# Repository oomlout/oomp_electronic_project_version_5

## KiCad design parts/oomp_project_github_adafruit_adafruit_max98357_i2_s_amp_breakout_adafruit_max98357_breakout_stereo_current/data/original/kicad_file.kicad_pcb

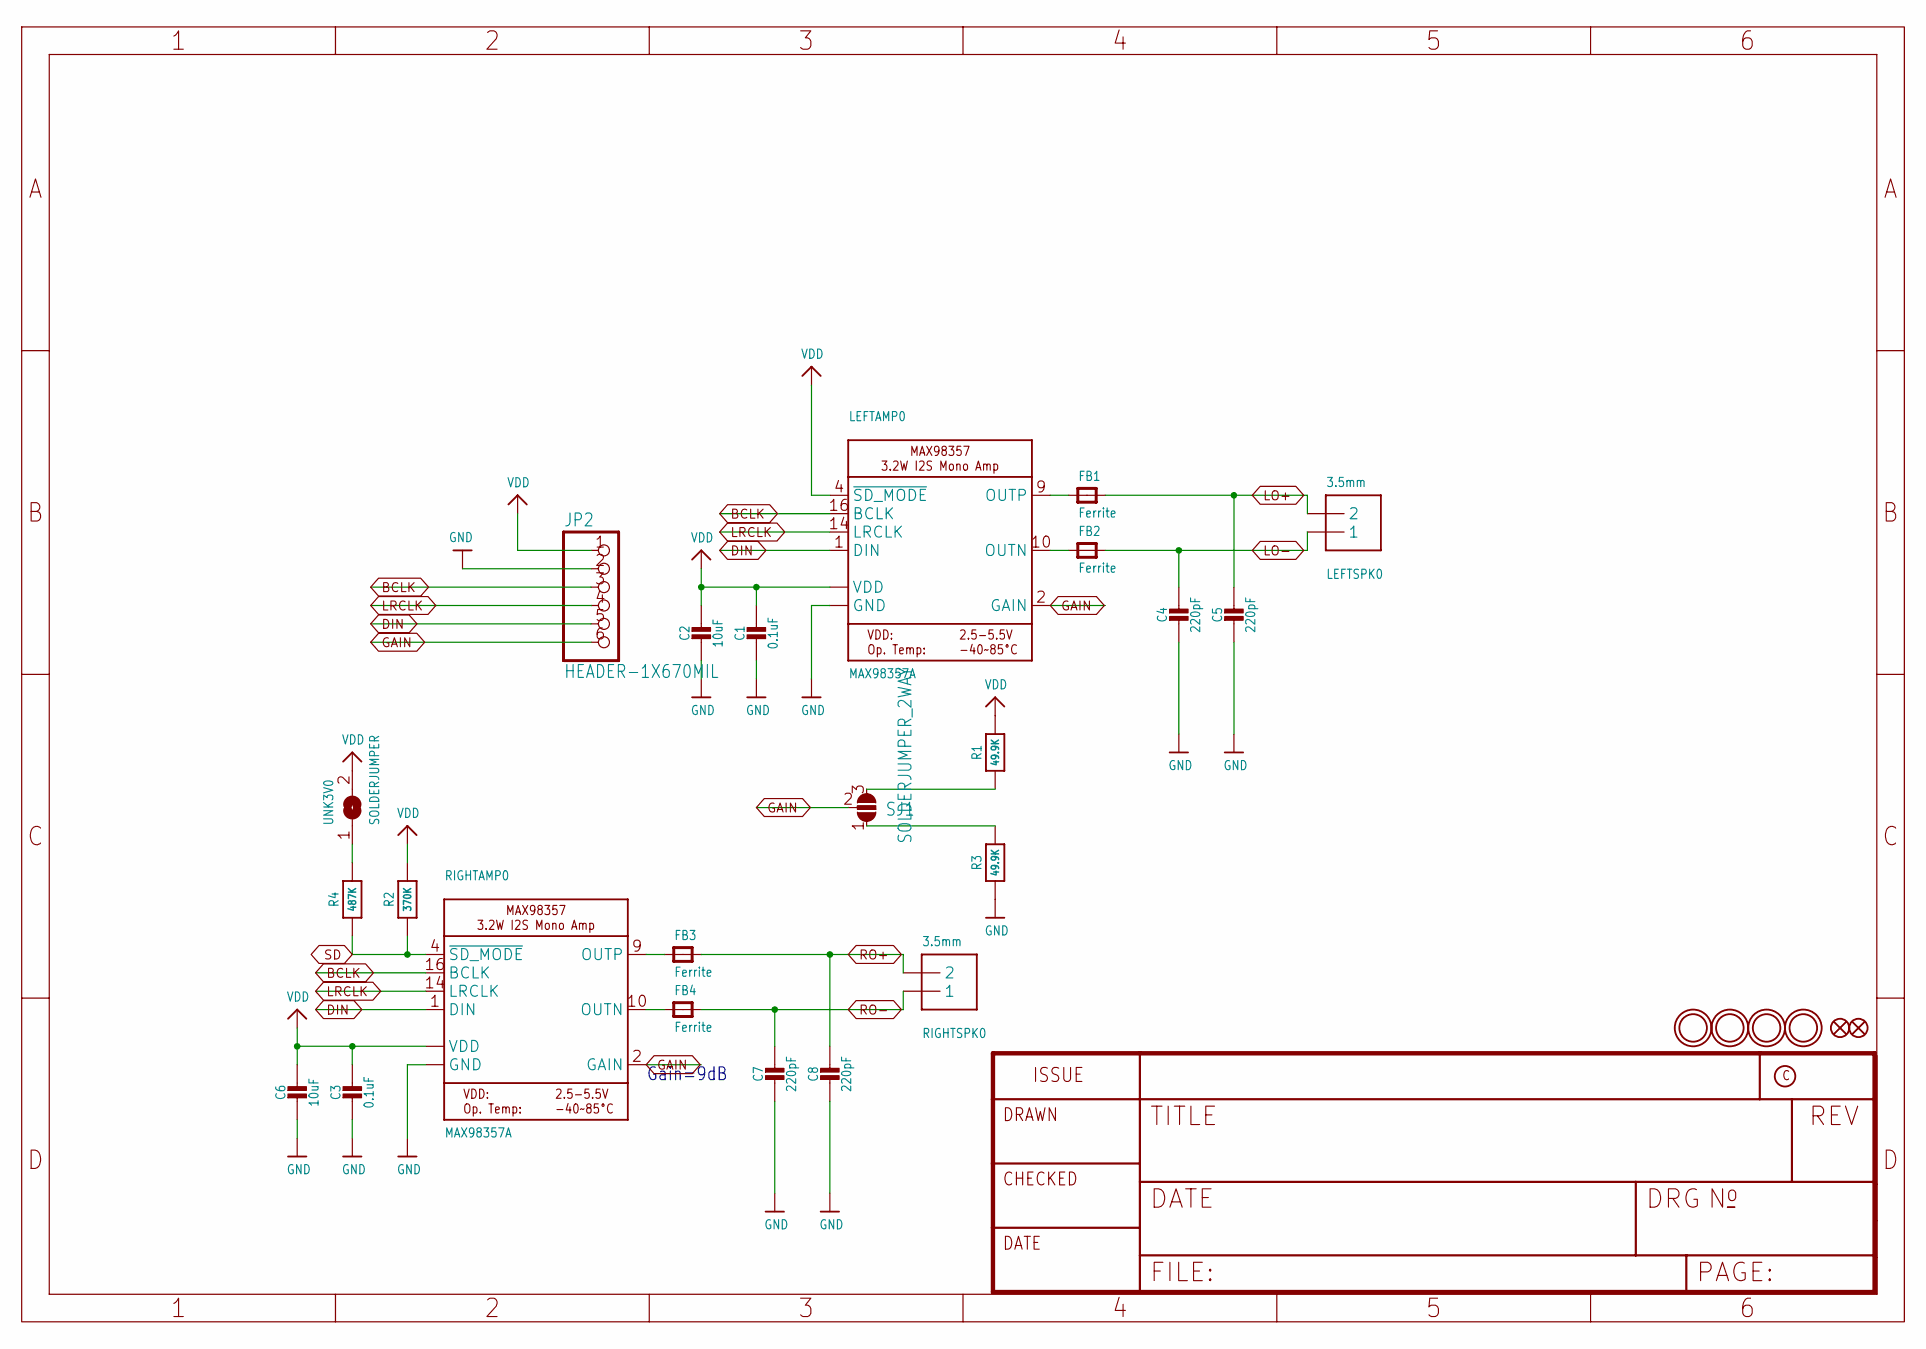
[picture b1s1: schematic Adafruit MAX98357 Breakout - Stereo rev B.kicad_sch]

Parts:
C1, C3: 0.1uF; 0603-NO
C2, C6: 10uF; 0805-NO
C4, C5, C7, C8: 220pF; 0603-NO
FB1, FB2, FB3, FB4: Ferrite; 0603-NO
FID1, FID2: FIDUCIAL_0.5MM
JP2: HEADER-1X670MIL; 1X06_ROUND_70
LEFTAMP0: MAX98357A; QFN16_3MM
LEFTSPK0: 3.5mm; TERMBLOCK_1X2-3.5MM
R1, R3: 49.9K; 0603-NO
R2: 370K; 0603-NO
R4: 487K; 0603-NO
RIGHTAMP0: MAX98357A; QFN16_3MM
RIGHTSPK0: 3.5mm; TERMBLOCK_1X2-3.5MM
SJ1: SOLDERJUMPER_2WAY; SOLDERJUMPER_2WAY_OPEN_NOPASTE
U$9, U$10, U$23, U$24: MOUNTINGHOLE2.5; MOUNTINGHOLE_2.5_PLATED
UNK3V0: SOLDERJUMPER; SOLDERJUMPER_ARROW_NOPASTE

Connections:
BCLK: JP2.3, LEFTAMP0.16 (BCLK), RIGHTAMP0.16 (BCLK)
DIN: JP2.5, LEFTAMP0.1 (DIN), RIGHTAMP0.1 (DIN)
GAIN: JP2.6, LEFTAMP0.2 (GAIN), RIGHTAMP0.2 (GAIN), SJ1.2
GND: C1.2, C2.2, C3.2, C4.2, C5.2, C6.2, C7.2, C8.2, JP2.2, LEFTAMP0.3 (GND), LEFTAMP0.11 (GND), LEFTAMP0.15 (GND), LEFTAMP0.THERMAL (GND), R3.1, RIGHTAMP0.3 (GND), RIGHTAMP0.11 (GND), RIGHTAMP0.15 (GND), RIGHTAMP0.THERMAL (GND)
LO+: C5.1, FB1.2, LEFTSPK0.2
LO-: C4.1, FB2.2, LEFTSPK0.1
LRCLK: JP2.4, LEFTAMP0.14 (LRCLK), RIGHTAMP0.14 (LRCLK)
unnamed: FB4.1, RIGHTAMP0.10 (OUTN)
unnamed: FB3.1, RIGHTAMP0.9 (OUTP)
unnamed: R3.2, SJ1.1
unnamed: R4.2, UNK3V0.1
unnamed: FB2.1, LEFTAMP0.10 (OUTN)
unnamed: FB1.1, LEFTAMP0.9 (OUTP)
unnamed: R1.1, SJ1.3
RO+: C8.1, FB3.2, RIGHTSPK0.2
RO-: C7.1, FB4.2, RIGHTSPK0.1
SD: R2.1, R4.1, RIGHTAMP0.4 (~SD_MODE)
VDD: C1.1, C2.1, C3.1, C6.1, JP2.1, LEFTAMP0.4 (~SD_MODE), LEFTAMP0.7 (VDD), LEFTAMP0.8 (VDD), R1.2, R2.2, RIGHTAMP0.7 (VDD), RIGHTAMP0.8 (VDD), UNK3V0.2

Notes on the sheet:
Gain=9dB

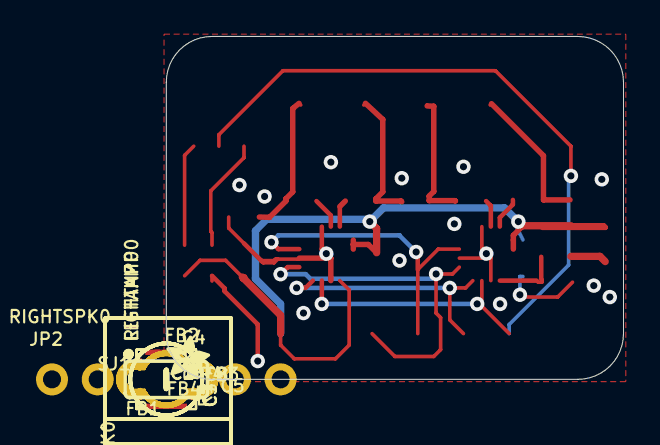
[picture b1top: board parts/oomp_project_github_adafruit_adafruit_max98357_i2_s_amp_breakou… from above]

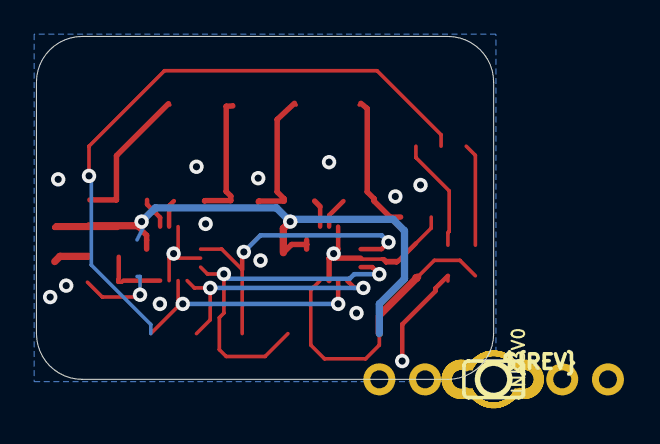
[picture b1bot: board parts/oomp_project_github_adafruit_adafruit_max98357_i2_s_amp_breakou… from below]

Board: 2 copper layers, 25.4 x 19.1 mm, 51 parts (6 on the bottom side), 18 nets.

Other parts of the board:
PLABEL0: PLABEL0
PLABEL1: PLABEL1
PLABEL2: PLABEL2
PLABEL3: PLABEL3
PLABEL4: PLABEL4
PLABEL5: PLABEL5
PLABEL6: PLABEL6
PLABEL7: PLABEL7
PLABEL8: PLABEL8
PLABEL9: PLABEL9
PLABEL10: PLABEL10
PLABEL11: PLABEL11
PLABEL12: PLABEL12
PLABEL13: PLABEL13
PLABEL14: PLABEL14
PLABEL15: PLABEL15
PLABEL16: PLABEL16
PLABEL17: PLABEL17
PLABEL18: PLABEL18
PLABEL19: PLABEL19
U$14: ADAFRUIT_2.5MM
U$15: PCBFEAT-REV-040

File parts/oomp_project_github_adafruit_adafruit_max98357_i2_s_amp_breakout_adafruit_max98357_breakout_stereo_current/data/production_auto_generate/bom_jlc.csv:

Comment,Designator,Footprint,LCSC Part #
,JP2,Adafruit MAX98357 Breakout - Stereo rev B-import-fps:1X06_ROUND_70,C37208
,U$14,Adafruit MAX98357 Breakout - Stereo rev B-import-fps:ADAFRUIT_2.5MM,
,U$15,Adafruit MAX98357 Breakout - Stereo rev B-import-fps:PCBFEAT-REV-040,
,PLABEL0,Adafruit MAX98357 Breakout - Stereo rev B-import-fps:PLABEL0,
,PLABEL1,Adafruit MAX98357 Breakout - Stereo rev B-import-fps:PLABEL1,
,PLABEL10,Adafruit MAX98357 Breakout - Stereo rev B-import-fps:PLABEL10,
,PLABEL11,Adafruit MAX98357 Breakout - Stereo rev B-import-fps:PLABEL11,
,PLABEL12,Adafruit MAX98357 Breakout - Stereo rev B-import-fps:PLABEL12,
,PLABEL13,Adafruit MAX98357 Breakout - Stereo rev B-import-fps:PLABEL13,
,PLABEL14,Adafruit MAX98357 Breakout - Stereo rev B-import-fps:PLABEL14,
,PLABEL15,Adafruit MAX98357 Breakout - Stereo rev B-import-fps:PLABEL15,
,PLABEL16,Adafruit MAX98357 Breakout - Stereo rev B-import-fps:PLABEL16,
,PLABEL17,Adafruit MAX98357 Breakout - Stereo rev B-import-fps:PLABEL17,
,PLABEL18,Adafruit MAX98357 Breakout - Stereo rev B-import-fps:PLABEL18,
,PLABEL19,Adafruit MAX98357 Breakout - Stereo rev B-import-fps:PLABEL19,
,PLABEL2,Adafruit MAX98357 Breakout - Stereo rev B-import-fps:PLABEL2,
,PLABEL3,Adafruit MAX98357 Breakout - Stereo rev B-import-fps:PLABEL3,
,PLABEL4,Adafruit MAX98357 Breakout - Stereo rev B-import-fps:PLABEL4,
,PLABEL5,Adafruit MAX98357 Breakout - Stereo rev B-import-fps:PLABEL5,
,PLABEL6,Adafruit MAX98357 Breakout - Stereo rev B-import-fps:PLABEL6,
,PLABEL7,Adafruit MAX98357 Breakout - Stereo rev B-import-fps:PLABEL7,
,PLABEL8,Adafruit MAX98357 Breakout - Stereo rev B-import-fps:PLABEL8,
,PLABEL9,Adafruit MAX98357 Breakout - Stereo rev B-import-fps:PLABEL9,
,UNK3V0,Adafruit MAX98357 Breakout - Stereo rev B-import-fps:SOLDERJUMPER_ARROW_NOPASTE,
0.1uF,"C1,C3",Adafruit MAX98357 Breakout - Stereo rev B-import-fps:0603-NO,C14663
10uF,"C2,C6",Adafruit MAX98357 Breakout - Stereo rev B-import-fps:0805-NO,
220pF,"C4,C5,C7,C8",Adafruit MAX98357 Breakout - Stereo rev B-import-fps:0603-NO,
3.5mm,"LEFTSPK0,RIGHTSPK0",Adafruit MAX98357 Breakout - Stereo rev B-import-fps:TERMBLOCK_1X2-3.5MM,
370K,R2,Adafruit MAX98357 Breakout - Stereo rev B-import-fps:0603-NO,
487K,R4,Adafruit MAX98357 Breakout - Stereo rev B-import-fps:0603-NO,
49.9K,"R1,R3",Adafruit MAX98357 Breakout - Stereo rev B-import-fps:0603-NO,
Ferrite,"FB1,FB2,FB3,FB4",Adafruit MAX98357 Breakout - Stereo rev B-import-fps:0603-NO,
MAX98357A,"LEFTAMP0,RIGHTAMP0",Adafruit MAX98357 Breakout - Stereo rev B-import-fps:QFN16_3MM,

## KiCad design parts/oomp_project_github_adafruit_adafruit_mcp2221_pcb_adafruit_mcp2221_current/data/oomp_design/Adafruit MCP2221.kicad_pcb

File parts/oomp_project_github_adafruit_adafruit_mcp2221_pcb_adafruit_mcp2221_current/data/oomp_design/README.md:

# OOMP KiCad design copy

Open `Adafruit MCP2221.kicad_pro` (or the `.kicad_pcb` / `.kicad_sch`) in KiCad. Local OOMP libraries are under `libraries/`. Original inputs are preserved in [../original/](../original/).

Only verified unchanged installed KiCad defaults were renamed. Modified, custom, unmatched and unavailable items remain unchanged. Soldering variants are never swapped during conversion. Existing pad coordinates, nets and UUIDs are preserved.

See [conversion_report.yaml](conversion_report.yaml) for every conversion and skip. Copy this directory before editing; regeneration refuses to overwrite edited design files.

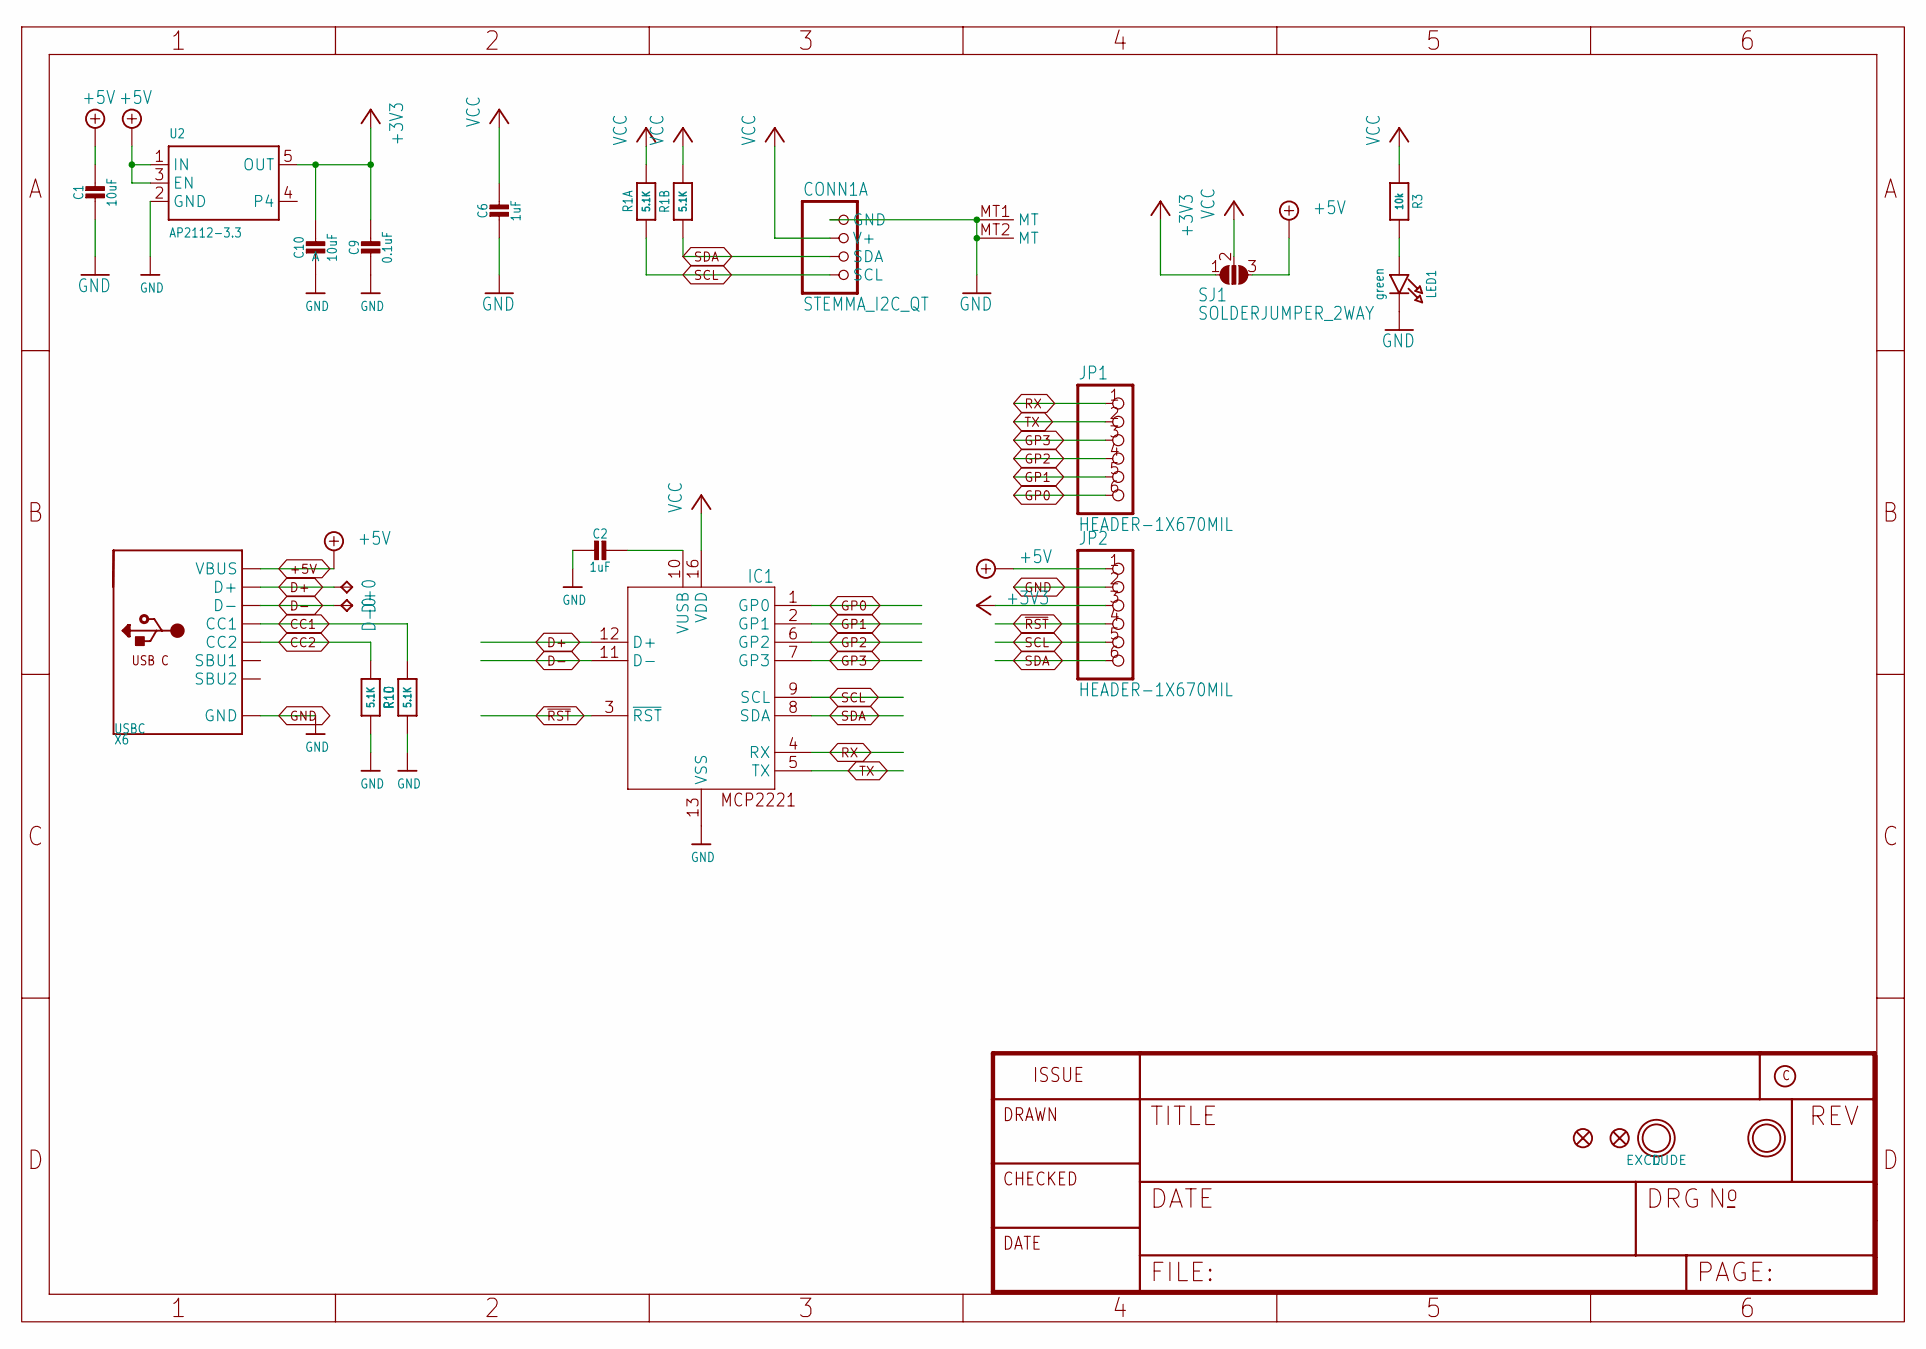
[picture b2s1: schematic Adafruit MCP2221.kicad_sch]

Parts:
C1, C10: 10uF; 0805-NO
C2, C6: 1uF; 0603-NO
C9: 0.1uF; 0603-NO
CONN1: STEMMA_I2C_QT; JST_SH4
D+0: TPTP17R; TP17R
D-0: TPTP17R; TP17R
FID1, FID2: FIDUCIAL_1MM
IC1: MCP2221_ML; QFN16_4MM
JP1, JP2: HEADER-1X670MIL; 1X06_ROUND_70
LED1: green; CHIPLED_0603_NOOUTLINE
R1: 5.1K; RESPACK_4X0603
R3: 10k; 0603-NO
SJ1: SOLDERJUMPER_2WAY; SOLDERJUMPER_2WAY_OPEN_NOPASTE
U2: AP2112-3.3; SOT23-5
U$6, U$7: MOUNTINGHOLE2.5; MOUNTINGHOLE_2.5_PLATED
X6: USBC; USB_C_CUSB31-CFM2AX-01-X

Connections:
+3V3: C9.1, C10.1, JP2.3, SJ1.1, U2.5 (OUT)
+5V: C1.1, JP2.1, SJ1.3, U2.1 (IN), U2.3 (EN), X6.A4B9 (VBUS), X6.B4A9 (VBUS)
CC1: R1.6 (2), X6.A5 (CC1)
CC2: R1.4 (1), X6.B5 (CC2)
D+: D+0.TP, IC1.12 (D+), X6.A6 (D+), X6.B6 (D+)
D-: D-0.TP, IC1.11 (D-), X6.A7 (D-), X6.B7 (D-)
GND: C1.2, C2.2, C6.2, C9.2, C10.2, CONN1.1 (GND), CONN1.MT1 (MT), CONN1.MT2 (MT), IC1.13 (VSS), JP2.2, LED1.C, R1.3 (1), R1.5 (2), U2.2 (GND), X6.A1B12 (GND), X6.B1A12 (GND)
GP0: IC1.1 (GP0), JP1.6
GP1: IC1.2 (GP1), JP1.5
GP2: IC1.6 (GP2), JP1.4
GP3: IC1.7 (GP3), JP1.3
unnamed: C2.1, IC1.10 (VUSB)
unnamed: LED1.A, R3.2
RX: IC1.4 (RX), JP1.1
SCL: CONN1.4 (SCL), IC1.9 (SCL), JP2.5, R1.1
SDA: CONN1.3 (SDA), IC1.8 (SDA), JP2.6, R1.2 (1)
TX: IC1.5 (TX), JP1.2
VCC: C6.1, CONN1.2 (V+), IC1.16 (VDD), R1.7 (2), R1.8 (2), R3.1, SJ1.2
~RST: IC1.3 (~RST), JP2.4

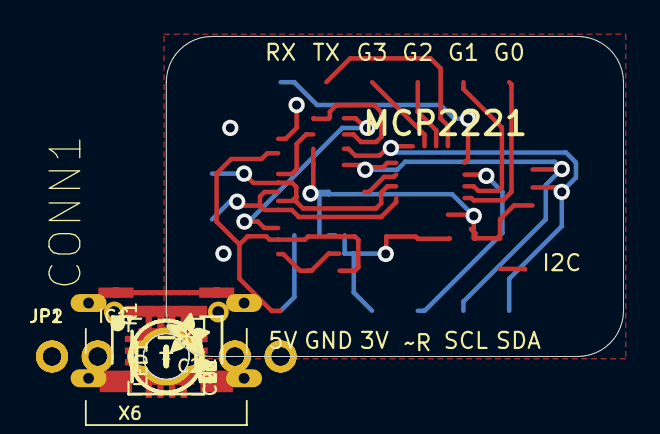
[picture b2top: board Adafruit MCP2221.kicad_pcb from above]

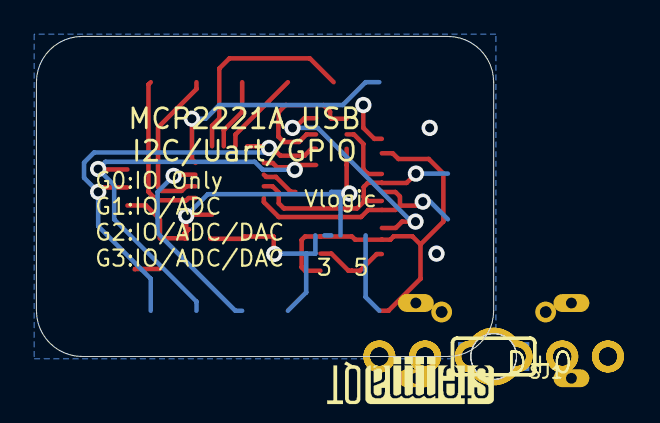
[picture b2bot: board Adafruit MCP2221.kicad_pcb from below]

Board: 2 copper layers, 25.4 x 17.8 mm, 25 parts (4 on the bottom side), 19 nets.

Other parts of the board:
U$2: ADAFRUIT_2.5MM
U$3: STEMMAQT
UNK_HOLE_0: dummyfp0
UNK_HOLE_1: dummyfp1

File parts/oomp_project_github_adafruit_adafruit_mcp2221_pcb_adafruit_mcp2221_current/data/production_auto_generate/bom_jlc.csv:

Comment,Designator,Footprint,LCSC Part #
,"JP1,JP2",Adafruit MCP2221-import-fps:1X06_ROUND_70,C37208
,U$2,Adafruit MCP2221-import-fps:ADAFRUIT_2.5MM,
,U$3,Adafruit MCP2221-import-fps:STEMMAQT,
0.1uF,C9,Adafruit MCP2221-import-fps:0603-NO,C14663
10k,R3,Adafruit MCP2221-import-fps:0603-NO,C98220
10uF,"C1,C10",Adafruit MCP2221-import-fps:0805-NO,
1uF,"C2,C6",Adafruit MCP2221-import-fps:0603-NO,C5673
5.1K,R1,Adafruit MCP2221-import-fps:RESPACK_4X0603,C23186
AP2112-3.3,U2,Adafruit MCP2221-import-fps:SOT23-5,
green,LED1,Adafruit MCP2221-import-fps:CHIPLED_0603_NOOUTLINE,
MCP2221_ML,IC1,Adafruit MCP2221-import-fps:QFN16_4MM,
STEMMA_I2C_QT,CONN1,Adafruit MCP2221-import-fps:JST_SH4,C160404
TPTP17R,"D+0,D-0",Adafruit MCP2221-import-fps:TP17R,
USBC,X6,Adafruit MCP2221-import-fps:USB_C_CUSB31-CFM2AX-01-X,

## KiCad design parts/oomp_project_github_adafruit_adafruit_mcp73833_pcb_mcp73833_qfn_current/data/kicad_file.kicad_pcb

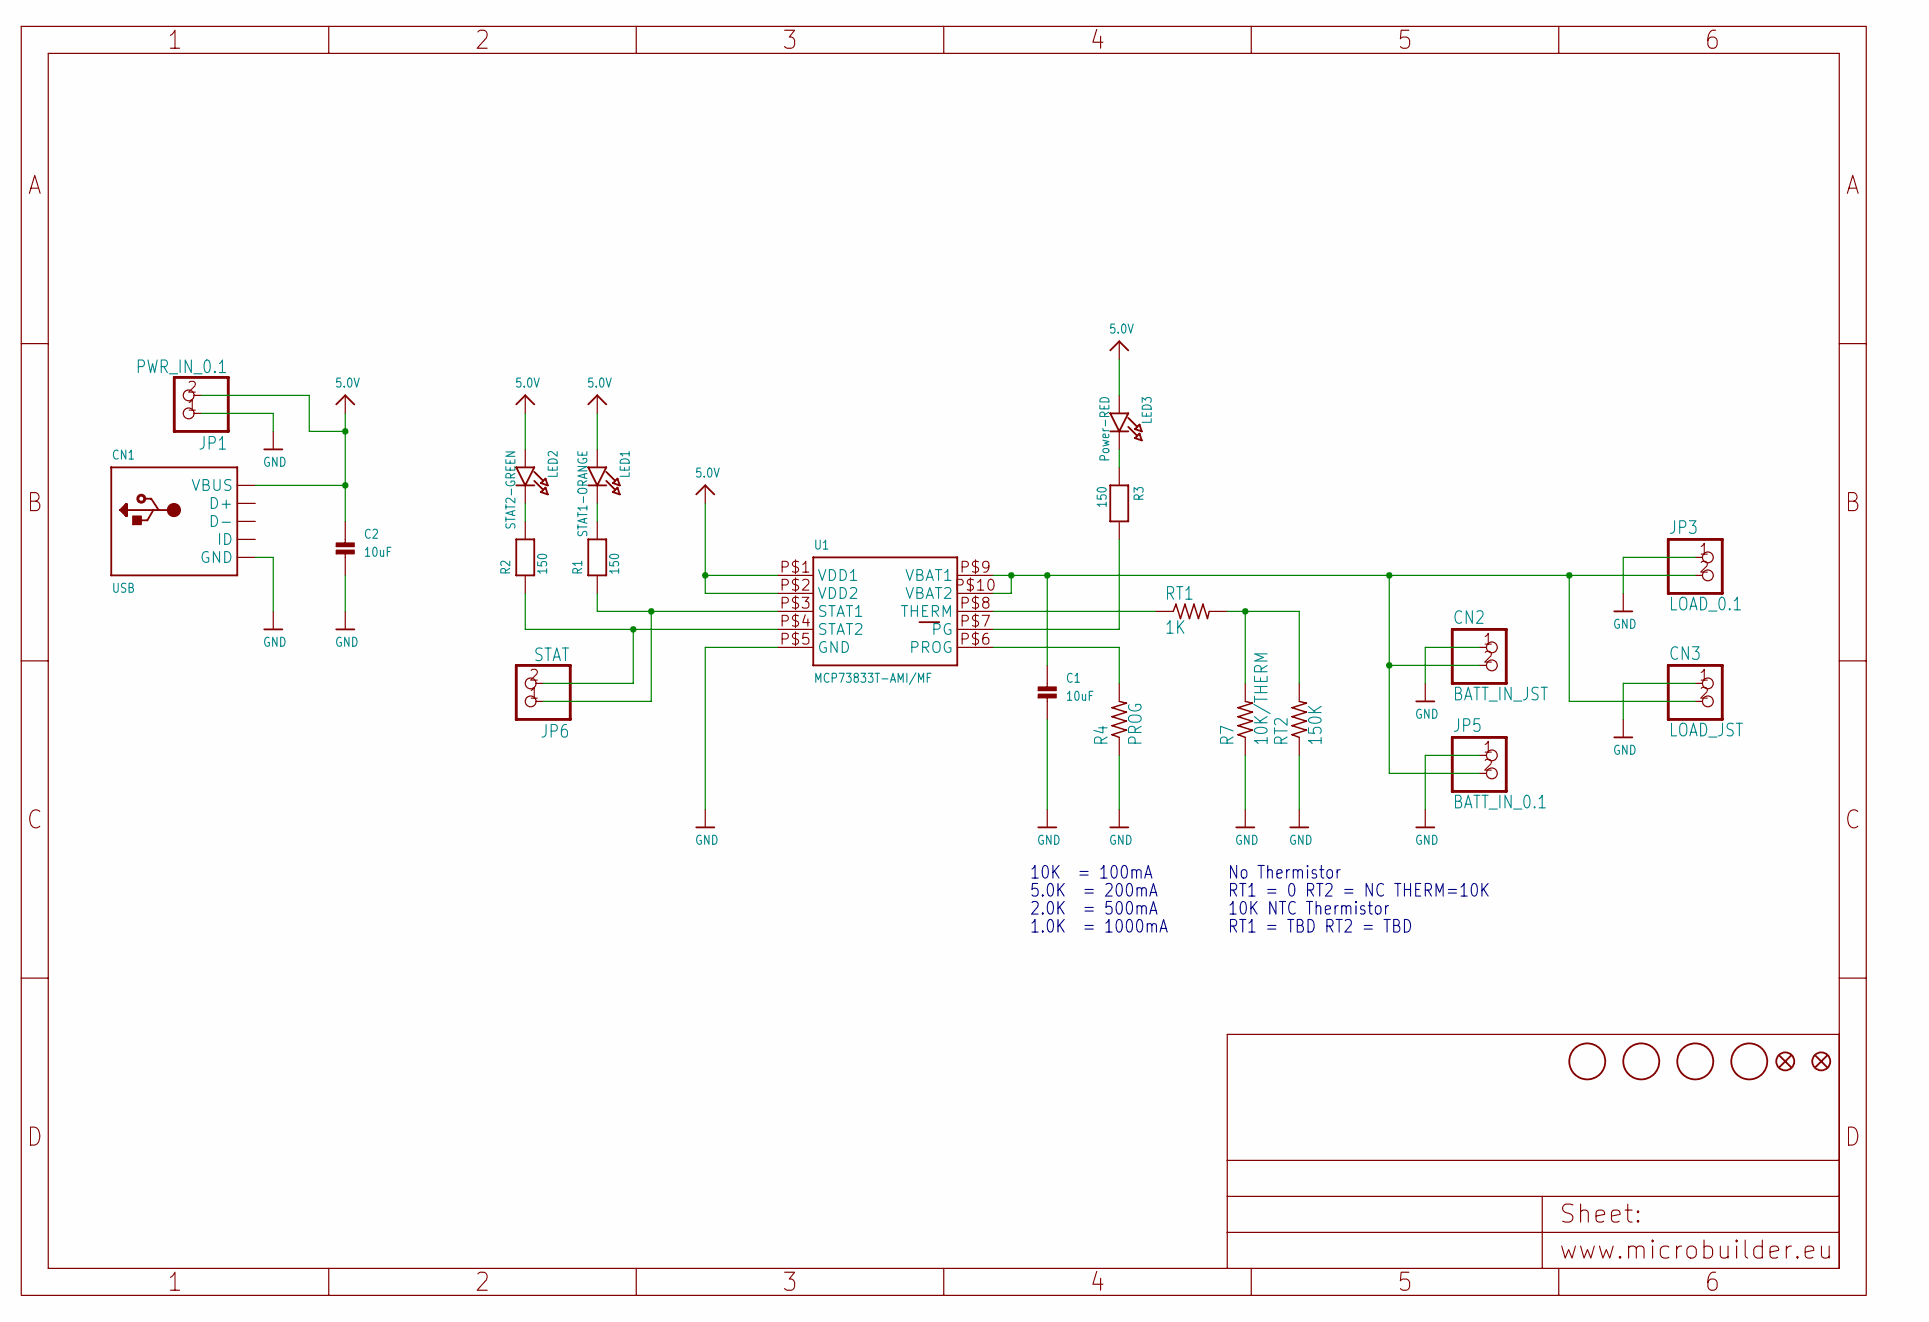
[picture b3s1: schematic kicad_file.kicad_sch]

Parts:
C1, C2: 10uF; 0805
CN1: USB; USB-MINIB_LARGER
CN2: BATT_IN_JST; JSTPH2
CN3: LOAD_JST; JSTPH2
JP1: PWR_IN_0.1; 1X02_OVAL
JP2, JP4: FIDUCIAL1.5X3; FIDUCIAL-1X2.5
JP3: LOAD_0.1; 1X02_OVAL
JP5: BATT_IN_0.1; 1X02_OVAL
JP6: STAT; 1X02_OVAL
LED1: STAT1-ORANGE; CHIPLED_0805
LED2: STAT2-GREEN; CHIPLED_0805
LED3: Power-RED; CHIPLED_0805
R1, R2, R3: 150; 0805
R4: PROG; 0805-THM
R7: 10K/THERM; 0805-THM
RT1: 1K; R0805
RT2: 150K; R0805
U1: MCP73833T-AMI/MF; DFN10_3X3MM
U$11, U$16, U$18, U$19: MOUNTINGHOLE2.0; MOUNTINGHOLE_2.0_PLATED

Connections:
5.0V: C2.1, CN1.VBUS, JP1.2, LED1.A, LED2.A, LED3.A, U1.P$1 (VDD1), U1.P$2 (VDD2)
BATT: C1.1, CN2.2, CN3.2, JP3.2, JP5.2, U1.P$9 (VBAT1), U1.P$10 (VBAT2)
GND: C1.2, C2.2, CN1.GND, CN2.1, CN3.1, JP1.1, JP3.1, JP5.1, R4.1, R7.1, RT2.1, U1.P$5 (GND)
unnamed: LED1.C, R1.2
unnamed: LED2.C, R2.2
unnamed: JP6.1, R1.1, U1.P$3 (STAT1)
unnamed: JP6.2, R2.1, U1.P$4 (STAT2)
unnamed: RT1.1, U1.P$8 (THERM)
unnamed: R3.2, U1.P$7 (PG)
unnamed: R7.2, RT1.2, RT2.2
unnamed: LED3.C, R3.1
unnamed: R4.2, U1.P$6 (PROG)

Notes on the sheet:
No Thermistor
10K = 100mA
10K NTC Thermistor
2.0K = 500mA
5.0K = 200mA
1.0K = 1000mA
RT1 = 0 RT2 = NC THERM=10K
RT1 = TBD RT2 = TBD

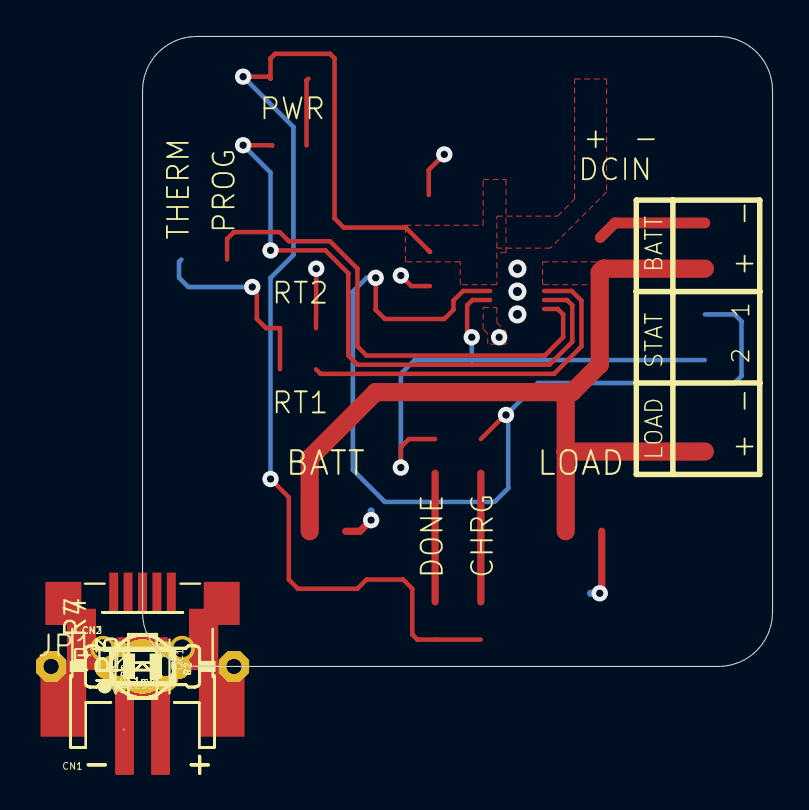
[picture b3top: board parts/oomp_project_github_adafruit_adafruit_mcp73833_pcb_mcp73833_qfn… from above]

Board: 2 copper layers, 35.0 x 35.0 mm, 27 parts (1 on the bottom side), 12 nets.

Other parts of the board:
U$14: ADAFRUIT200MIL

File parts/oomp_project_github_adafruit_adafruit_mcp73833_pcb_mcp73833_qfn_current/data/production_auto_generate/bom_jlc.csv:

Comment,Designator,Footprint,LCSC Part #
,U$14,MCP73833_QFN_v1.0-import-fps:ADAFRUIT200MIL,
10K/THERM,R7,MCP73833_QFN_v1.0-import-fps:0805-THM,C17414
10uF,"C1,C2",MCP73833_QFN_v1.0-import-fps:0805,
150,"R1,R2,R3",MCP73833_QFN_v1.0-import-fps:0805,C2907300
150K,RT2,MCP73833_QFN_v1.0-import-fps:R0805,C2907228
1K,RT1,MCP73833_QFN_v1.0-import-fps:R0805,C17513
BATT_IN_0.1,JP5,MCP73833_QFN_v1.0-import-fps:1X02_OVAL,C492401
BATT_IN_JST,CN2,MCP73833_QFN_v1.0-import-fps:JSTPH2,
FIDUCIAL1.5X3,"JP2,JP4",MCP73833_QFN_v1.0-import-fps:FIDUCIAL-1X2.5,
LOAD_0.1,JP3,MCP73833_QFN_v1.0-import-fps:1X02_OVAL,C492401
LOAD_JST,CN3,MCP73833_QFN_v1.0-import-fps:JSTPH2,
MCP73833T-AMI/MF,U1,MCP73833_QFN_v1.0-import-fps:DFN10_3X3MM,
Power-RED,LED3,MCP73833_QFN_v1.0-import-fps:CHIPLED_0805,
PROG,R4,MCP73833_QFN_v1.0-import-fps:0805-THM,
PWR_IN_0.1,JP1,MCP73833_QFN_v1.0-import-fps:1X02_OVAL,C492401
STAT,JP6,MCP73833_QFN_v1.0-import-fps:1X02_OVAL,C492401
STAT1-ORANGE,LED1,MCP73833_QFN_v1.0-import-fps:CHIPLED_0805,
STAT2-GREEN,LED2,MCP73833_QFN_v1.0-import-fps:CHIPLED_0805,
USB,CN1,MCP73833_QFN_v1.0-import-fps:USB-MINIB_LARGER,

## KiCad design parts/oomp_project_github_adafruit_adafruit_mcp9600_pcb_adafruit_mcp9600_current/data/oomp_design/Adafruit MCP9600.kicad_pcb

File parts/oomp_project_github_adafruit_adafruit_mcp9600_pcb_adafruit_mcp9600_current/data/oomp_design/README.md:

# OOMP KiCad design copy

Open `Adafruit MCP9600.kicad_pro` (or the `.kicad_pcb` / `.kicad_sch`) in KiCad. Local OOMP libraries are under `libraries/`. Original inputs are preserved in [../original/](../original/).

Only verified unchanged installed KiCad defaults were renamed. Modified, custom, unmatched and unavailable items remain unchanged. Soldering variants are never swapped during conversion. Existing pad coordinates, nets and UUIDs are preserved.

See [conversion_report.yaml](conversion_report.yaml) for every conversion and skip. Copy this directory before editing; regeneration refuses to overwrite edited design files.

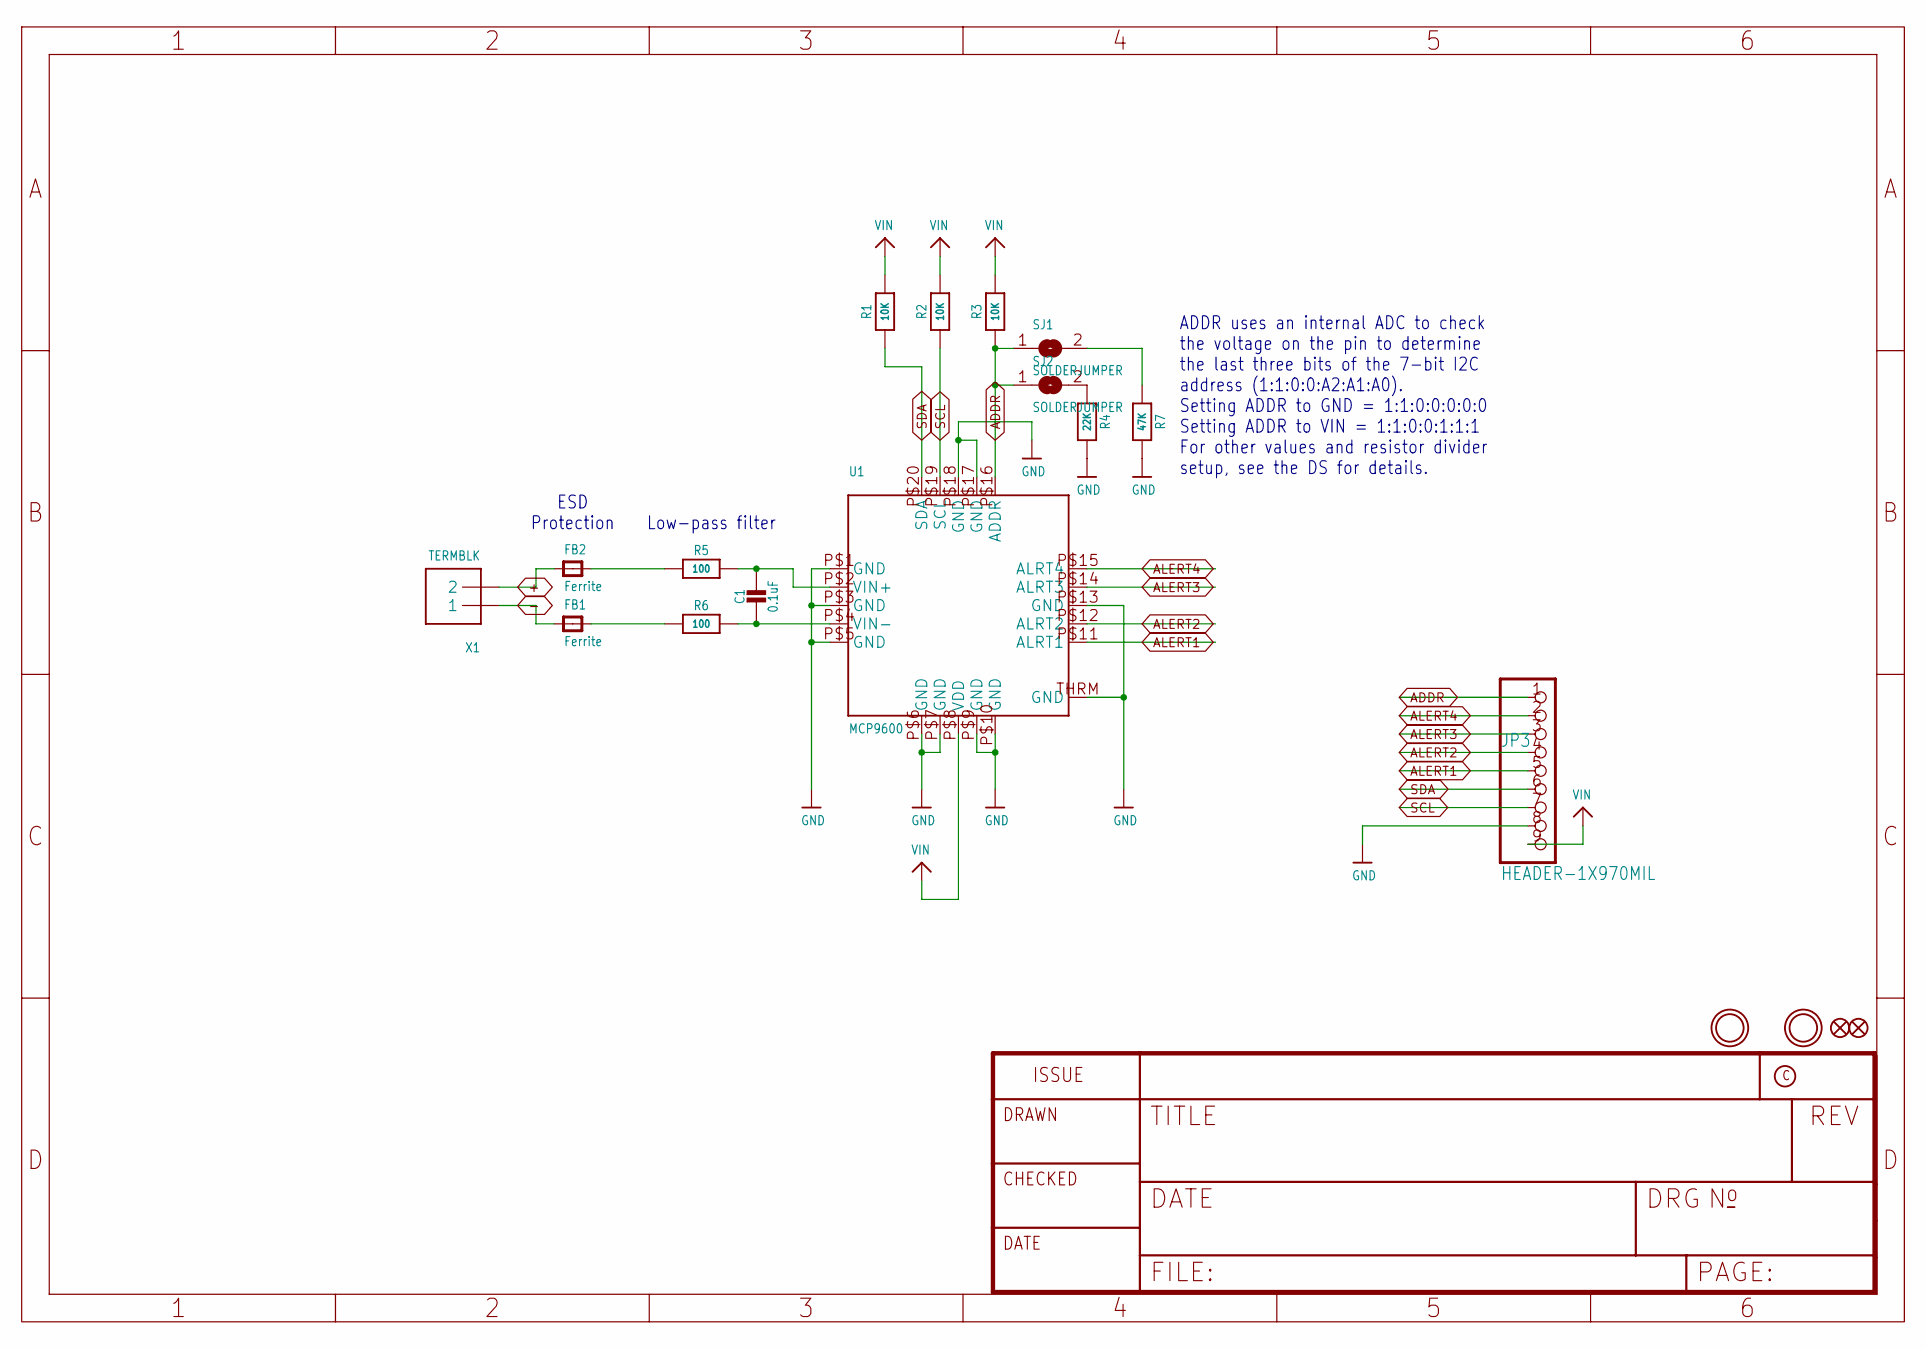
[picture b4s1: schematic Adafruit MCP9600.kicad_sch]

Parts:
C1: 0.1uF; 0603-NO
FB1, FB2: Ferrite; 0805-NO
FID1, FID2: FIDUCIAL_1MM
JP3: HEADER-1X970MIL; 1X09_ROUND_70
R1, R2, R3: 10K; 0603-NO
R4: 22K; 0603-NO
R5, R6: 100; 0603-NO
R7: 47K; 0603-NO
SJ1, SJ2: SOLDERJUMPER; SOLDERJUMPER_ARROW_NOPASTE
U1: MCP9600; VQFN20_5MM
U$1, U$3: MOUNTINGHOLE2.5; MOUNTINGHOLE_2.5_PLATED
X1: TERMBLK; TERMBLOCK_1X2-3.5MM

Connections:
+: FB2.1, X1.2
-: FB1.1, X1.1
ADDR: JP3.1, R3.1, SJ1.1, SJ2.1, U1.P$16 (ADDR)
ALERT1: JP3.5, U1.P$11 (ALRT1)
ALERT2: JP3.4, U1.P$12 (ALRT2)
ALERT3: JP3.3, U1.P$14 (ALRT3)
ALERT4: JP3.2, U1.P$15 (ALRT4)
GND: JP3.8, R4.2, R7.2, U1.P$1 (GND), U1.P$3 (GND), U1.P$5 (GND), U1.P$6 (GND), U1.P$7 (GND), U1.P$9 (GND), U1.P$10 (GND), U1.P$13 (GND), U1.P$17 (GND), U1.P$18 (GND), U1.THRM (GND)
unnamed: C1.1, R5.2, U1.P$2 (VIN+)
unnamed: C1.2, R6.2, U1.P$4 (VIN-)
unnamed: FB1.2, R6.1
unnamed: FB2.2, R5.1
unnamed: R7.1, SJ1.2
unnamed: R4.1, SJ2.2
SCL: JP3.7, R2.1, U1.P$19 (SCL)
SDA: JP3.6, R1.1, U1.P$20 (SDA)
VIN: JP3.9, R1.2, R2.2, R3.2, U1.P$8 (VDD)

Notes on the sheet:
ESD Protection
ADDR uses an internal ADC to check the voltage on the pin to determine the last three bits of the 7-bit I2C address (1:1:0:0:A2:A1:A0). Setting ADDR to GND = 1:1:0:0:0:0:0 Setting ADDR to VIN = 1:1:0:0:1:1:1 For other values and resistor divider setup, see the DS for details.
Low-pass filter

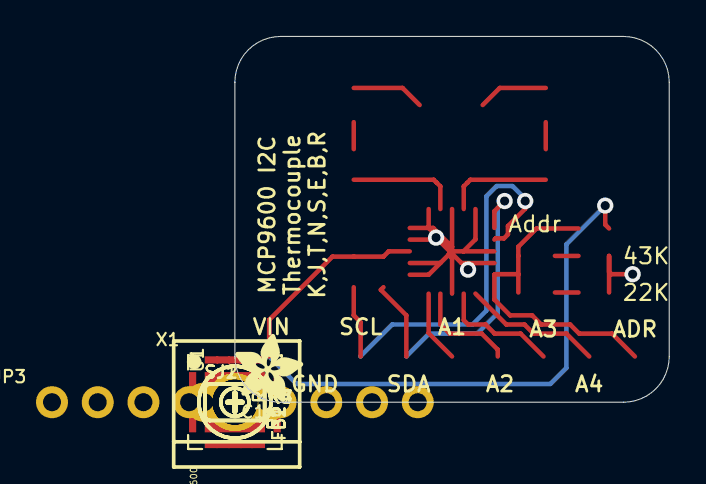
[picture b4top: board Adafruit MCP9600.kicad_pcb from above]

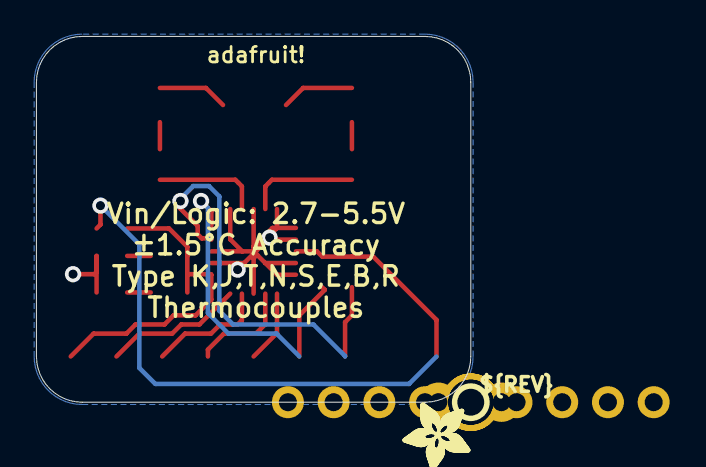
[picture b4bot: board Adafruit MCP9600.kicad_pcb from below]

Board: 2 copper layers, 24.1 x 20.3 mm, 25 parts (3 on the bottom side), 17 nets.

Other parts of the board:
U$16, U$19, U$20: ADAFRUIT_3.5MM
U$17: SYMBOL_PLUS
U$18: SYMBOL_MINUS
U$21: PCBFEAT-REV-040

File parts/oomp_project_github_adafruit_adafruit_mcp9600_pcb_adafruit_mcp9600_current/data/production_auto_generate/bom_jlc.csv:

Comment,Designator,Footprint,LCSC Part #
,JP3,Adafruit MCP9600-import-fps:1X09_ROUND_70,C2932701
,"U$16,U$19,U$20",Adafruit MCP9600-import-fps:ADAFRUIT_3.5MM,
,U$21,Adafruit MCP9600-import-fps:PCBFEAT-REV-040,
,U$18,Adafruit MCP9600-import-fps:SYMBOL_MINUS,
,U$17,Adafruit MCP9600-import-fps:SYMBOL_PLUS,
0.1uF,C1,Adafruit MCP9600-import-fps:0603-NO,C14663
100,"R5,R6",Adafruit MCP9600-import-fps:0603-NO,C22775
10K,"R1,R2,R3",Adafruit MCP9600-import-fps:0603-NO,C98220
22K,R4,Adafruit MCP9600-import-fps:0603-NO,C31850
47K,R7,Adafruit MCP9600-import-fps:0603-NO,C2907042
Ferrite,"FB1,FB2",Adafruit MCP9600-import-fps:0805-NO,
MCP9600,U1,Adafruit MCP9600-import-fps:VQFN20_5MM,
TERMBLK,X1,Adafruit MCP9600-import-fps:TERMBLOCK_1X2-3.5MM,
